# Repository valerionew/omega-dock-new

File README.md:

# Omega dock\new

Project released under CC-BY-SA 4.0 license  

1. [Project status](#project-status)  
1. [Project description](#project-description)  
1. [BOM](#bom)  
1. [Photos](#photos) 

<a href="https://oshpark.com/shared_projects/xYpCcduu"></img></a>

If you want to discuss the project, join [the thread in the onion community forum](https://community.onion.io/topic/2284/my-omega-2-2-dock-new)

## Project status
Current version is tested and working.  
No new versions are planned at the moment

## Project description 
This is my dock\new project: it's a small dock (same size as the mini dock and the omega) for the Onion Omega 2 and 2+.

I needed the smallest dock i could do, that featured:

* Ethernet
* Type A USB host
* Micro USB for power

It has an onboard linear voltage regulation (i didn't bother going with a switching one for such low power), magnetics integrated in the RJ45 connector to save space, USB host ESD protection (diode array), USB host PTC fuse.

On the left side there is the RJ45 connector and nothing on the back side of the board, so that you can easily access the MicroSD card on the Omega 2+.
On the right side (the antenna side of the omega) you have the USB type A connector, facing outwards, and the microusb connector for power, facing inwards.

The first version, v0.9, had some issues with the ethernet. Currently i've released v1.0 that solves all the issues, adds a led to check power and, making a better use of the space, the RJ45 connector doesn't protrude anymore. I haven't ordered the v1.0 PCBs yet, but the circuit is tested.

I've chosen 0805 passives, 1206 ptc fuse, big smd electrolitic caps, a SOT223 (the classic 1117) for power regulation and a SOT23-6 for usb host protection, so it can all be easily handsoldered with just a plain soldering iron. Probably the hardest part to handsolder is the SOT23-6 but it's easily doable by hand.

The components and board cost for the prototype it's arround 10 to 15€ per board.

## BOM
|    Symbol   |                 Package                | Quantity |    Valore   |                          Note                          |
|:-----------:|:--------------------------------------:|:--------:|:-----------:|:------------------------------------------------------:|
| C1          | CP_Elec_4x5.3                          |     1    | 10uF        | 10V or higher                                          |
| C2          | CP_Elec_6.3x5.3                        |     1    | 100uF       | 10V or higher                                          |
| C3, C4      | 0805                                   |     2    | 100nF       |                                                        |
| C5          | 0805                                   |     1    | 1uF         |                                                        |
| D1          | 1206                                   |     1    | PWR         | Amber LED                                              |
| F1          | 1206                                   |     1    | 1.5A        | PTC Fuse                                               |
| J1          | USB_A                                  |     1    | USB_A       | MOLEX 67643-3910                                       |
| J2          | USB_Micro-B                            |     1    | USB_PWR     | ADAM TECH MCR-AB1-S-RA-SMT-CS1-TR                      |
| J3          | RJ45_TRAFO_AMPHENOL                    |     1    | RJ45-TRAFO  | AMPHENOL LMJ1598824110DT39                             |
| R1,R2,R3,R4 | 0805                                   |     4    | 50R         | Ethernet termination resistors: should be 1% or better |
| R5          | 0805                                   |     1    | 150R        |                                                        |
| U1          | SOT23-6                                |     1    | USBLC6-2SC6 |                                                        |
| U2          | SOT223                                 |     1    | AP111733    |                                                        |
| U3          | Socket_Strip_Straight_1x16_Pitch2.00mm |     2    | OMEGA_2_2+  | Two 2mm 1x16 strip connectors                          |

## Build instructions 
The following is my response to [issue #10](https://github.com/valerionew/omega-dock-new/issues/10), where i described the assembly process and tips and tricks that i use. I think it might be helpfull to report it here.

First of all: 
**I strongly encourage anyone who has any basic electronic soldering experience, to get the boards from wherever they want and solder his own. It's much more satisfying and, if you've never done SMD before, you'll have a chance to learn it**. 
Why do i say so? Because this board has a very few parts, big SMD pads and reasonably big components. Once you learn SMD soldering, they are even easier to solder than through hole parts. Don't feel uncomfortable, SMD parts are great.

### Boards
The easiest thing is to just get it from OSHPark. They have good prices, deliver three boards and the shipping is free worldwide. I've already uploaded my v1.0 design on their website, so that you can order it with just a few clicks.
[Here](https://oshpark.com/shared_projects/xYpCcduu) is the link.

### Soldering
So, what you need to get started? 
* **A soldering iron**. I use the *Hakko FX-888D* with the tip that comes with it, but that's upon your preferences and your budget. A cheaper AliExpress iron will also do the job.
* **Solder**. I use *Sn60Pb40 solder*, and i recommend you to do the same. I prefer 0.5 mm, but you can go with whatever you want, i suggest to stay in the 0.4-0.75 range.
* **Some flux**. I use it in a *felt tip dispensing pen*, but again, you can use whatever you prefer.
* **Solder wick**. I use whatever i can find, not really a problem. 
* **Fine tweezers**, if possible ESD safe. I use the *Vetus ESD-11*, but yet again you can use whatever you want.
* **Patience!** A lot of that! After all, you are learning something new

That's all you need. Given that you already have a soldering iron, the other things are cheap. Patience is free.
About the method, these are the steps i do for a 2 pin component:
1. Put some flux on the pads. No skimping with that
1. Heat one pad with your iron and put some solder on it. You'll learn the right amount with the time, but don't worry, you'll have the chance to remove the excess with the wick after (or before, if you prefer) you've soldered the part. 
1. Grab the part with the tweezers, reheat the pad and place the component. Don't be too quick or solder won't stick to the part. Hold the part with the tweezers until the solder becomes solid. Then release.
1. Solder the other pin, adding some solder.
1. Inspect. Check, by eyes or with a magnifying glass, that there is a joint between each pad and the component.

That's it. For ICs and parts with more pins i usually solder one pad first, make sure that the alignment is correct, then solder the diagonally opposite pin, then all the others, but the steps are basically the same.
Same rule as THT soldering applies: lower profile parts first.

### Parts
For the passives you can basically pick whatever you want, as long as they are the same value, same package, and same tolerance. All those specs and quantities are shown in the table up here.

The only two ICs here are U1 and U2. 

U1 is USBLC6-2SC6. This is a TVS and diode protection array, specifically designed for USB ESD protection. It is not *strictly* necessary, but given that it's a very cheap part and provides additional protection, why not use it. Moreover, the docks from omega use a similar protection too. However, if you aren't going to use it short pad 1 with pad 6, and pad 3 with pad 4. **DON'T short pad 2 and pad 5. That would be a short on the power supply**

U2 is just a basic 1117-3.3v. A linear 3.3v regulator. You can pick a 1117 3.3v or even another linear regulator, as long as it has the same package, the same footprint, and it's capable of supplying at least 500mA.

There is a 1206 PTC fuse, anything from 1A to 1.5A should be good. 

Connector choice is critical to this project. I've indicated the exact part that i've used. If you can't find them you have two choices:
1. Pick another part. You can go to whatever supplier, shop or distributor and find a part that would fit mechanically in the pins. Make sure to check the distance between the mechanical mounting pins and the electrical pins. Also  **check the pinout, they are not always the same, especially in RJ45 connectors.**. 
In USB and RJ45 connectors, the distance from the last pin in the back, and the back of the connector **is critical**: it should be **no more** than what is in the parts that i've indicated, or the two polarized capacitors won't fit. If the RJ45 part has LED pins, they can be cut before soldering, so no big deal.
1. Modify the board. You can download the KiCad files and modify the footprints in order to fit your particular connector. Again,  **check the pinout**.

Then, pick two parts of 1x16 2mm female header, and you are done. 

## Photos

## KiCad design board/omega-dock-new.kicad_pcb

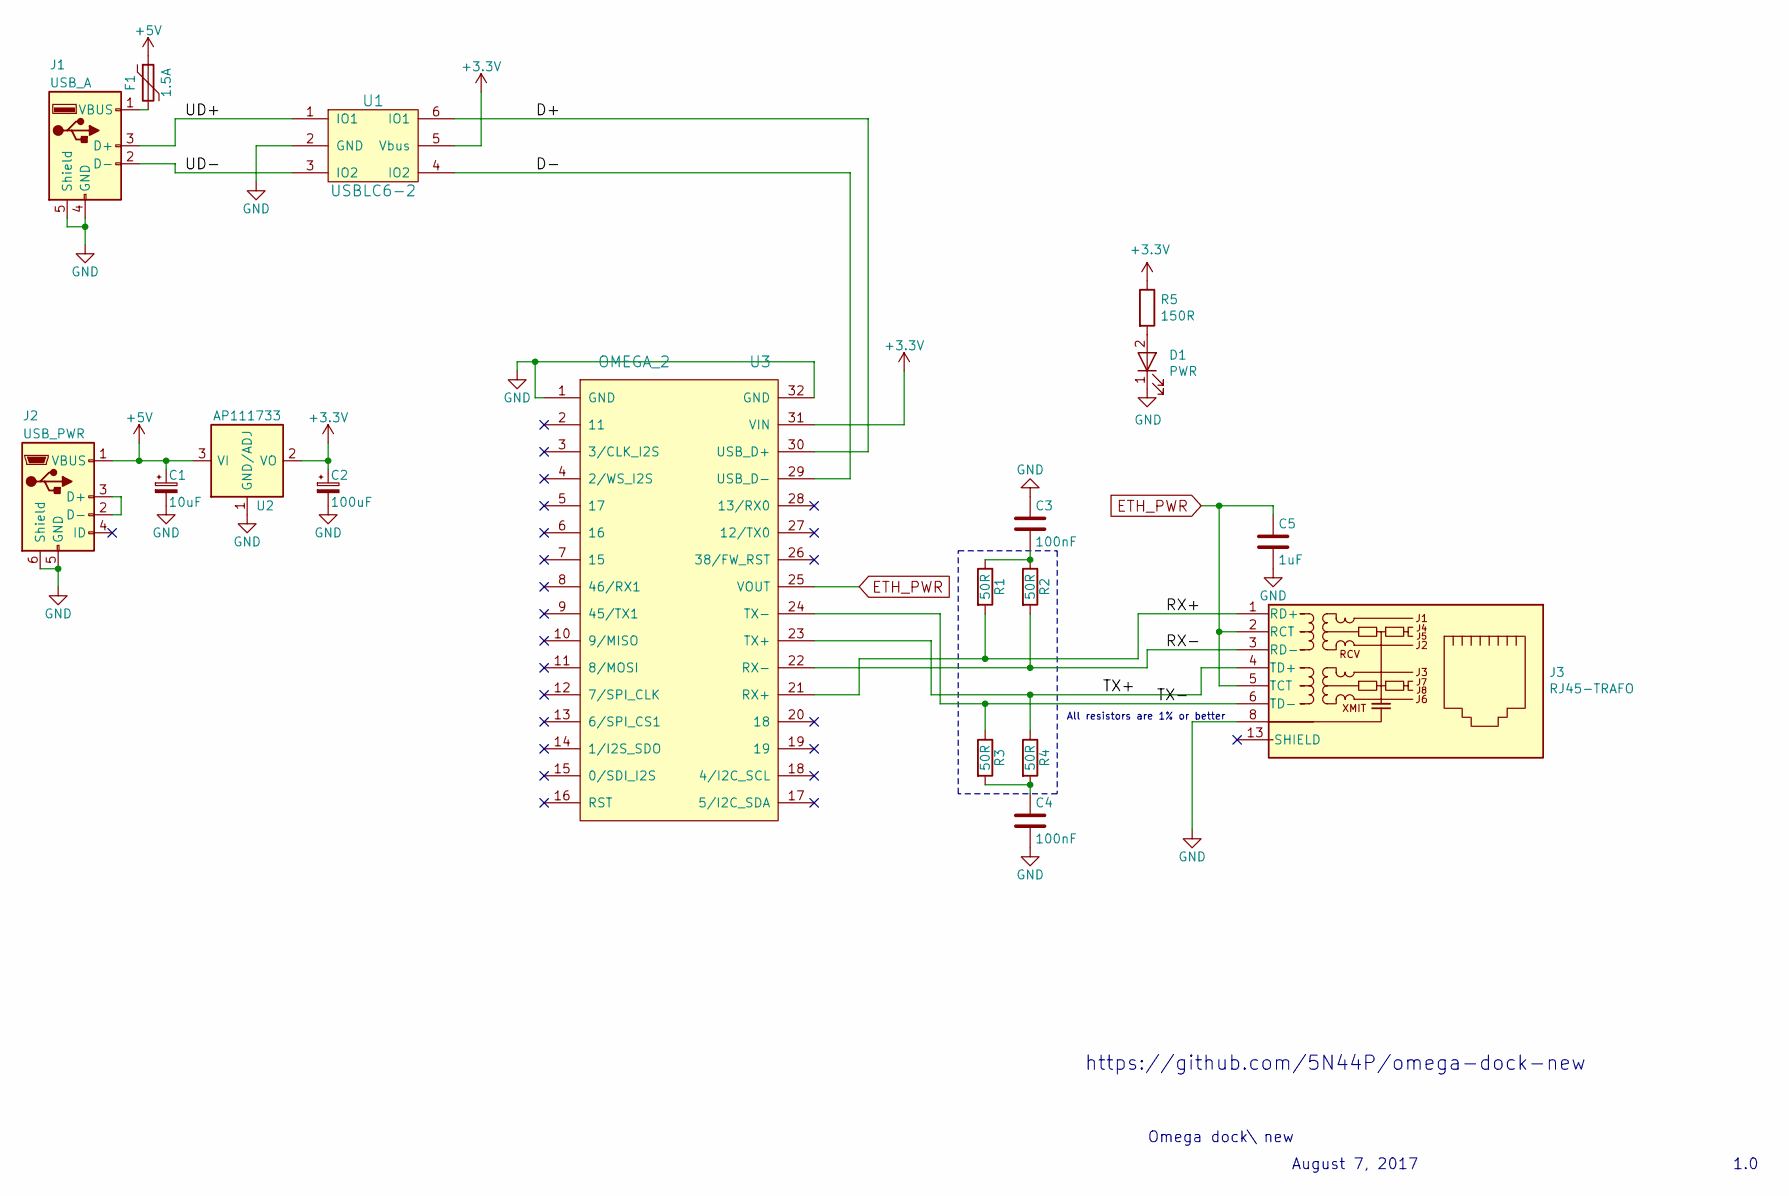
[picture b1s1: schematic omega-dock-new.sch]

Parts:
C1: 10uF; CP_Elec_4x5.3
C2: 100uF; CP_Elec_6.3x5.3
C3, C4: 100nF; C_0805_HandSoldering
C5: 1uF; C_0805_HandSoldering
D1: PWR; LED_1206_HandSoldering
F1: 1.5A; C_1206_HandSoldering
J1: USB_A
J2: USB_PWR; USB_Micro-B
J3: RJ45-TRAFO; RJ45_TRAFO_AMPHENOL
R1, R2, R3, R4: 50R; R_0805_HandSoldering
R5: 150R; R_0805_HandSoldering
U1: USBLC6-2; SOT-23-6_Handsoldering
U2: AP111733; SOT-223
U3: OMEGA_2

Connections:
+3V3: C2.1, R5.1, U1.5 (Vbus), U2.2 (VO), U2.4 (VO), U3.31 (VIN)
+5V: C1.1, F1.1, J2.1 (VBUS), U2.3 (VI)
/D+: U1.6 (IO1), U3.30 (USB_D+)
/D-: U1.4 (IO2), U3.29 (USB_D-)
/RX+: J3.1 (RD+), R1.2, U3.21 (RX+)
/RX-: J3.3 (RD-), R2.2, U3.22 (RX-)
/TX+: J3.4 (TD+), R4.1, U3.23 (TX+)
/TX-: J3.6 (TD-), R3.1, U3.24 (TX-)
/UD+: J1.3 (D+), U1.1 (IO1)
/UD-: J1.2 (D-), U1.3 (IO2)
ETH_PWR: C5.1, J3.2 (RCT), J3.5 (TCT), U3.25 (VOUT)
GND: C1.2, C2.2, C3.1, C4.2, C5.2, D1.1 (K), J1.4 (GND), J1.5 (Shield), J2.5 (GND), J2.6 (Shield), J3.8, U1.2 (GND), U2.1 (GND/ADJ), U3.1 (GND), U3.32 (GND)
unnamed: C3.2, R1.1, R2.1
unnamed: C4.1, R3.2, R4.2
unnamed: D1.2 (A), R5.2
unnamed: F1.2, J1.1 (VBUS)
unnamed: J2.2 (D-), J2.3 (D+)

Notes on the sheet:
Omega dock\ new
August 7, 2017
1.0
https://github.com/5N44P/omega-dock-new
All resistors are 1% or better

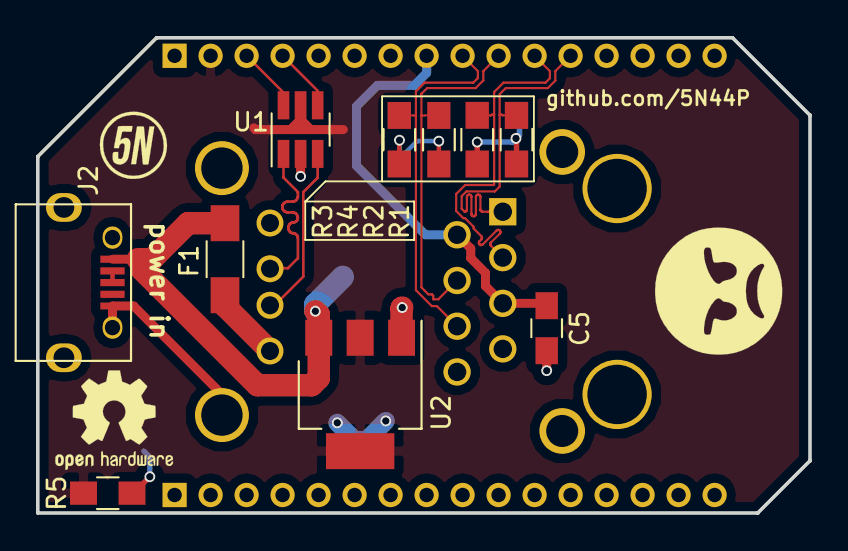
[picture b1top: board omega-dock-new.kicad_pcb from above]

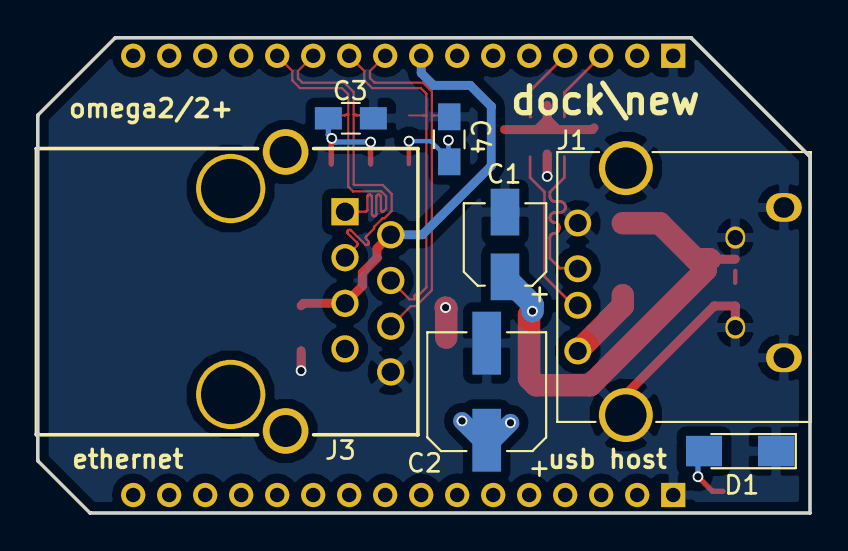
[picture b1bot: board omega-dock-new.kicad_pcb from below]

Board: 2 copper layers, 42.9 x 26.4 mm, 18 parts (7 on the bottom side), 17 nets.

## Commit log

2017-06-28 Create LICENSE
2017-06-28 Added board kicad project
2017-06-28 Added board image
2017-06-28 added schematic pdf
2017-08-03 Updated project status
2017-08-07 v1.0 fixes #1, fixes #2, fixes #3, fixes #4, fixes #5, fixes #7, fixes #8
2017-08-07 v1.0 schematic
2017-08-10 Obsolete
2017-08-10 added photos
2017-08-10 added layouts
2017-08-11 Added BOM
2017-08-16 :sunny:
2017-08-18 moved file
2017-09-12 minor errors
2018-01-30 Created .gitattributes
    make kicad files detectable by github language stats (linguist)
2018-03-08 Modified linguist attributes
2021-10-13 Added order from oshpark link
2022-07-08 Fix in readme

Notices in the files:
README.md:
License: CC BY-SA 4.0
